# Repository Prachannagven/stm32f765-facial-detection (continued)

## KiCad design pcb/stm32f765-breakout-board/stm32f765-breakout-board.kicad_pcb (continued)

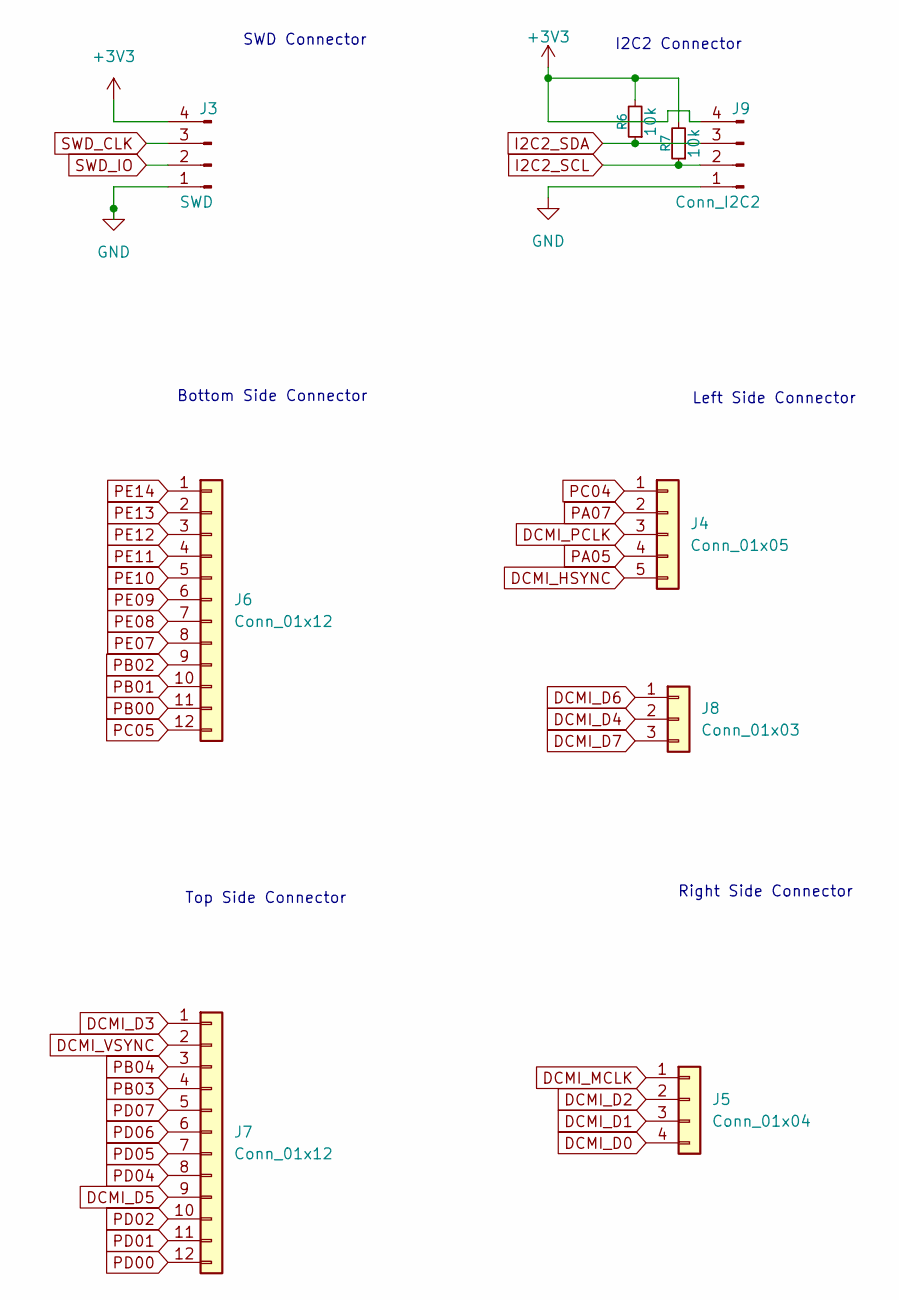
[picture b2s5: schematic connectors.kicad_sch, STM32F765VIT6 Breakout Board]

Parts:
J3: SWD; PinHeader_1x04_P2.54mm_Vertical
J4: Conn_01x05; PinHeader_1x05_P2.54mm_Vertical
J5: Conn_01x04; PinHeader_1x04_P2.54mm_Vertical
J6, J7: Conn_01x12; PinHeader_1x12_P2.54mm_Vertical
J8: Conn_01x03; PinHeader_1x03_P2.54mm_Vertical
J9: Conn_I2C2; PinHeader_1x04_P2.54mm_Vertical
R6, R7: 10k; R_0805_2012Metric_Pad1.20x1.40mm_HandSolder

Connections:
+3V3: J3.4, J9.4, R6.2, R7.2; also elsewhere on the board
DCMI_D0: J5.4; also elsewhere on the board
DCMI_D1: J5.3; also elsewhere on the board
DCMI_D2: J5.2; also elsewhere on the board
DCMI_D3: J7.1; also elsewhere on the board
DCMI_D4: J8.2; also elsewhere on the board
DCMI_D5: J7.9; also elsewhere on the board
DCMI_D6: J8.1; also elsewhere on the board
DCMI_D7: J8.3; also elsewhere on the board
DCMI_HSYNC: J4.5; also elsewhere on the board
DCMI_MCLK: J5.1; also elsewhere on the board
DCMI_PCLK: J4.3; also elsewhere on the board
DCMI_VSYNC: J7.2; also elsewhere on the board
GND: J3.1, J9.1; also elsewhere on the board
I2C2_SCL: J9.2, R7.1; also elsewhere on the board
I2C2_SDA: J9.3, R6.1; also elsewhere on the board
PA05: J4.4; also elsewhere on the board
PA07: J4.2; also elsewhere on the board
PB00: J6.11; also elsewhere on the board
PB01: J6.10; also elsewhere on the board
PB02: J6.9; also elsewhere on the board
PB03: J7.4; also elsewhere on the board
PB04: J7.3; also elsewhere on the board
PC04: J4.1; also elsewhere on the board
PC05: J6.12; also elsewhere on the board
PD00: J7.12; also elsewhere on the board
PD01: J7.11; also elsewhere on the board
PD02: J7.10; also elsewhere on the board
PD04: J7.8; also elsewhere on the board
PD05: J7.7; also elsewhere on the board
PD06: J7.6; also elsewhere on the board
PD07: J7.5; also elsewhere on the board
PE07: J6.8; also elsewhere on the board
PE08: J6.7; also elsewhere on the board
PE09: J6.6; also elsewhere on the board
PE10: J6.5; also elsewhere on the board
PE11: J6.4; also elsewhere on the board
PE12: J6.3; also elsewhere on the board
PE13: J6.2; also elsewhere on the board
PE14: J6.1; also elsewhere on the board
SWD_CLK: J3.3; also elsewhere on the board
SWD_IO: J3.2; also elsewhere on the board

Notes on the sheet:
I2C2 Connector
Top Side Connector
SWD Connector
Bottom Side Connector
Left Side Connector
Right Side Connector

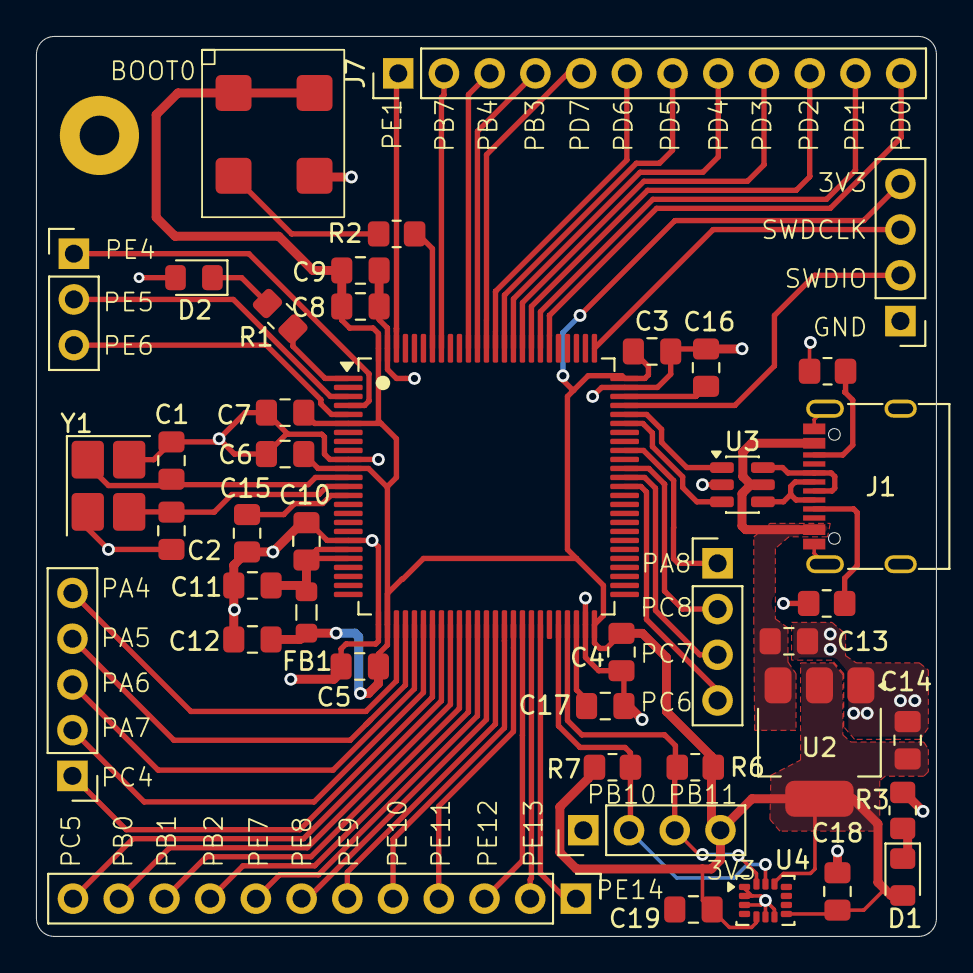
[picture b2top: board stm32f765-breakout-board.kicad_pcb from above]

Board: 2 copper layers, 50.0 x 50.0 mm, 44 parts (0 on the bottom side), 60 nets.

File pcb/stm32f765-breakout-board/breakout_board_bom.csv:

Robu SKU,Reference,Qty,Value,DNP,Exclude from BOM,Exclude from Board,Footprint,Datasheet
595331,"C1,C2",2,10p,,,,Capacitor_SMD:C_0805_2012Metric_Pad1.18x1.45mm_HandSolder,~
595344,"C3,C4,C5,C6,C7,C8,C13,C14,C15",9,100n,,,,Capacitor_SMD:C_0805_2012Metric_Pad1.18x1.45mm_HandSolder,~
1544904,C9,1,10u,,,,Capacitor_SMD:C_0805_2012Metric_Pad1.18x1.45mm_HandSolder,~
595338,C10,1,10n,,,,Capacitor_SMD:C_0805_2012Metric_Pad1.18x1.45mm_HandSolder,~
1089873,"C11,C12",2,1u,,,,Capacitor_SMD:C_0805_2012Metric_Pad1.18x1.45mm_HandSolder,~
R136885,"C16,C17",2,2.2u,,,,Capacitor_SMD:C_0805_2012Metric_Pad1.18x1.45mm_HandSolder,~
,D1,1,LED,,,,LED_SMD:LED_0805_2012Metric_Pad1.15x1.40mm_HandSolder,~
R112445,FB1,1,FerriteBead,,,,Inductor_SMD:L_0805_2012Metric_Pad1.05x1.20mm_HandSolder,~
R243053,J1,1,16P_USB_C,,,,Connector_USB:USB_C_Receptacle_G-Switch_GT-USB-7010ASV,https://robu.in/wp-content/uploads/2025/08/C165948.pdf
,J3,1,SWD,,,,Connector_PinHeader_2.54mm:PinHeader_1x04_P2.54mm_Vertical,~
,J4,1,Conn_01x05,,,,Connector_PinHeader_2.54mm:PinHeader_1x05_P2.54mm_Vertical,~
,J5,1,Conn_01x04,,,,Connector_PinHeader_2.54mm:PinHeader_1x04_P2.54mm_Vertical,~
,"J6,J7",2,Conn_01x12,,,,Connector_PinHeader_2.54mm:PinHeader_1x12_P2.54mm_Vertical,~
,J8,1,Conn_01x03,,,,Connector_PinHeader_2.54mm:PinHeader_1x03_P2.54mm_Vertical,~
,J9,1,Conn_I2C2,,,,Connector_PinHeader_2.54mm:PinHeader_1x04_P2.54mm_Vertical,~
R242850,R2,1,10k,,,,Resistor_SMD:R_0805_2012Metric_Pad1.20x1.40mm_HandSolder,~
"R138408,R143534","R3,R6,R7",3,1k5,,,,Resistor_SMD:R_0805_2012Metric_Pad1.20x1.40mm_HandSolder,~
R218648,"R4,R5",2,5k1,,,,Resistor_SMD:R_0805_2012Metric_Pad1.20x1.40mm_HandSolder,~
1883759,SW2,1,SW_BOOT0,,,,stm32_f765_breakout_library:new_4.5x4.5_mm_tactile_button_1883759,~
,U1,1,STM32F765VIT6,,,,Package_QFP:LQFP-100_14x14mm_P0.5mm,https://www.st.com/resource/en/datasheet/stm32f765vi.pdf
,U2,1,AMS1117-3.3,,,,Package_TO_SOT_SMD:SOT-223-3_TabPin2,http://www.advanced-monolithic.com/pdf/ds1117.pdf
,U3,1,USBLC6-2SC6,,,,Package_TO_SOT_SMD:SOT-23-6,https://www.st.com/resource/en/datasheet/usblc6-2.pdf
,Y1,1,16MHz,,,,Crystal:Crystal_SMD_3225-4Pin_3.2x2.5mm_HandSoldering,~

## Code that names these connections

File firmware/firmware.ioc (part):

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Mcu.Name=STM32F765V(G-I)Tx
Mcu.Package=LQFP100
Mcu.UserName=STM32F765VITx
PA0/WKUP.Mode=Asynchronous
PA0/WKUP.Signal=UART4_TX
PA1.Mode=Asynchronous
PA1.Signal=UART4_RX
PA11.Mode=Device_Only
PA11.Signal=USB_OTG_FS_DM
PA12.Mode=Device_Only
PA12.Signal=USB_OTG_FS_DP
PA13.Mode=Serial_Wire
PA13.Signal=SYS_JTMS-SWDIO
PA14.Mode=Serial_Wire
PA14.Signal=SYS_JTCK-SWCLK
PA4.GPIOParameters=GPIO_Speed,GPIO_PuPd
PA4.GPIO_PuPd=GPIO_PULLDOWN
PA4.GPIO_Speed=GPIO_SPEED_FREQ_VERY_HIGH
PA4.Mode=Slave_8_bits_External_Synchro
PA4.Signal=DCMI_HSYNC
PA6.GPIOParameters=GPIO_Speed,GPIO_PuPd
PA6.GPIO_PuPd=GPIO_PULLDOWN
PA6.GPIO_Speed=GPIO_SPEED_FREQ_VERY_HIGH
PA6.Mode=Slave_8_bits_External_Synchro
PA6.Signal=DCMI_PIXCLK
PA7.Signal=GPIO_Output
PA8.Mode=Clock-out-1
PA8.Signal=RCC_MCO_1
PB0.Signal=GPIO_Output
PB1.Signal=GPIO_Output
PB10.Mode=I2C
PB10.Signal=I2C2_SCL
PB11.Mode=I2C
PB11.Signal=I2C2_SDA
PB12.Mode=Asynchronous
PB12.Signal=UART5_RX
PB13.Mode=Asynchronous
PB13.Signal=UART5_TX
PB2.Signal=GPIO_Output
PB3.Mode=Full_Duplex_Master
PB3.Signal=SPI1_SCK
PB4.Mode=Full_Duplex_Master
PB4.Signal=SPI1_MISO
PB7.GPIOParameters=GPIO_Speed,GPIO_PuPd
PB7.GPIO_PuPd=GPIO_PULLDOWN
PB7.GPIO_Speed=GPIO_SPEED_FREQ_VERY_HIGH
PB7.Mode=Slave_8_bits_External_Synchro
PB7.Signal=DCMI_VSYNC
PC4.Signal=GPIO_Output
PC5.Signal=GPIO_Output
PC6.GPIOParameters=GPIO_Speed,GPIO_PuPd
PC6.GPIO_PuPd=GPIO_PULLDOWN
PC6.GPIO_Speed=GPIO_SPEED_FREQ_VERY_HIGH
PC6.Mode=Slave_8_bits_External_Synchro
PC6.Signal=DCMI_D0
PC7.GPIOParameters=GPIO_Speed,GPIO_PuPd
PC7.GPIO_PuPd=GPIO_PULLDOWN
PC7.GPIO_Speed=GPIO_SPEED_FREQ_VERY_HIGH
PC7.Mode=Slave_8_bits_External_Synchro
PC7.Signal=DCMI_D1
PC8.GPIOParameters=GPIO_Speed,GPIO_PuPd
PC8.GPIO_PuPd=GPIO_PULLDOWN
PC8.GPIO_Speed=GPIO_SPEED_FREQ_VERY_HIGH
PC8.Mode=Slave_8_bits_External_Synchro
PC8.Signal=DCMI_D2
PD0.Mode=CAN_Activate
PD0.Signal=CAN1_RX
PD1.Mode=CAN_Activate
PD1.Signal=CAN1_TX
PD2.Signal=GPIO_Output
PD3.GPIOParameters=GPIO_Speed,GPIO_PuPd
PD3.GPIO_PuPd=GPIO_PULLDOWN
PD3.GPIO_Speed=GPIO_SPEED_FREQ_VERY_HIGH
PD3.Mode=Slave_8_bits_External_Synchro
PD3.Signal=DCMI_D5
PD4.Signal=GPIO_Output
PD5.Mode=Asynchronous
PD5.Signal=USART2_TX
PD6.Mode=Asynchronous
PD6.Signal=USART2_RX
PD7.Mode=Full_Duplex_Master
PD7.Signal=SPI1_MOSI
PE1.GPIOParameters=GPIO_Speed,GPIO_PuPd
PE1.GPIO_PuPd=GPIO_PULLDOWN
PE1.GPIO_Speed=GPIO_SPEED_FREQ_VERY_HIGH
PE1.Mode=Slave_8_bits_External_Synchro
PE1.Signal=DCMI_D3
PE10.Signal=GPIO_Output
PE11.Signal=GPIO_Output
PE12.Mode=Full_Duplex_Slave
PE12.Signal=SPI4_SCK
PE13.Mode=Full_Duplex_Slave
PE13.Signal=SPI4_MISO
PE14.Mode=Full_Duplex_Slave
PE14.Signal=SPI4_MOSI
PE4.GPIOParameters=GPIO_Speed,GPIO_PuPd
PE4.GPIO_PuPd=GPIO_PULLDOWN
PE4.GPIO_Speed=GPIO_SPEED_FREQ_VERY_HIGH
PE4.Mode=Slave_8_bits_External_Synchro
PE4.Signal=DCMI_D4
PE5.GPIOParameters=GPIO_Speed,GPIO_PuPd
PE5.GPIO_PuPd=GPIO_PULLDOWN
PE5.GPIO_Speed=GPIO_SPEED_FREQ_VERY_HIGH
PE5.Mode=Slave_8_bits_External_Synchro
PE5.Signal=DCMI_D6
PE6.GPIOParameters=GPIO_Speed,GPIO_PuPd
PE6.GPIO_PuPd=GPIO_PULLDOWN
PE6.GPIO_Speed=GPIO_SPEED_FREQ_VERY_HIGH
PE6.Mode=Slave_8_bits_External_Synchro
PE6.Signal=DCMI_D7
PE7.Signal=GPIO_Output
PE8.Signal=GPIO_Output
PE9.Signal=GPIO_Output
PH0/OSC_IN.Mode=HSE-External-Oscillator
PH0/OSC_IN.Signal=RCC_OSC_IN
PH1/OSC_OUT.Mode=HSE-External-Oscillator
PH1/OSC_OUT.Signal=RCC_OSC_OUT
RCC.HSE_VALUE=16000000
board=custom

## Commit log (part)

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2026-04-01 finished stm32f7 breakout board
2026-04-06 added lsm6dsl to pcb and ordered v3
2026-04-12 final breakout board ordered
2026-04-17 Updated titleblock on f765 breakout pcb
2026-05-01 Added on board LED to PCB and blinky for board
    v6 of the PCB now has an in built on board LED to PE02, to allow for
    faster debugging.
    The first assembled prototype finally worked, and a blinky sketch was
    flashed to test. Relevant code has been added to firmware.
2026-05-01 Updated gitignore
2026-05-23 v1 of PCB completed
    Complete schematic completed with motor drivers, sensor integration and
    others.
2026-05-23 Removed unnecessary files
2026-05-24 New layout for pcb
2026-05-24 main is good
2026-05-24 WIP - arranging components in updated PCB
2026-05-24 WIP - Power routing done. Signal routing remaining
    - Power routing from USB and battery to MCP and AMS completed.
    - Power routing from motors to battery completed
    - Grounds have not been routed yet, leaving to the end.
    - Most 3V3 pads haven't been routed yet, leaving to the end
2026-05-24 v2.0 of PCB completed
    Updated routing to have USB port in center of top.
    Shrank overall size to 50x50 mm
    Layout is now ground+signal >> ground >> 3V3 >> signal
    TODO: Add stitching vias between ground on top and second layer?
2026-05-27 add: added images and updated readme
    - Removed redundant schematic files.
    - Added images of v2 of the PCB
    - Updated readme to include hardware design
2026-05-27 add: added watermark to pcb
2026-05-28 feat: added touch points to PCB
    Took advice from reddit to improve the PCB schematic
2026-06-03 v3 of PCB made. ov7670 implementation guide added
2026-06-11 firmware: added ov7670 camera support and updated gitignore
2026-06-11 fw: Updated with sram
2026-06-11 fw: ov7670 camra colors corrected
2026-06-11 fw: adding images back
2026-06-11 stopped working after timing changed to F0??
2026-06-11 somewhat right??
2026-06-11 small updates, nothing really
2026-06-12 usb has stopped working?
2026-06-12 Successful vertical bars, but no all colors yet
2026-06-20 added more images during testing
2026-06-21 set up python training for cca inferenceand CMake for c compilation
2026-06-24 updated jpg to pngs in the test files for easier reading in C
